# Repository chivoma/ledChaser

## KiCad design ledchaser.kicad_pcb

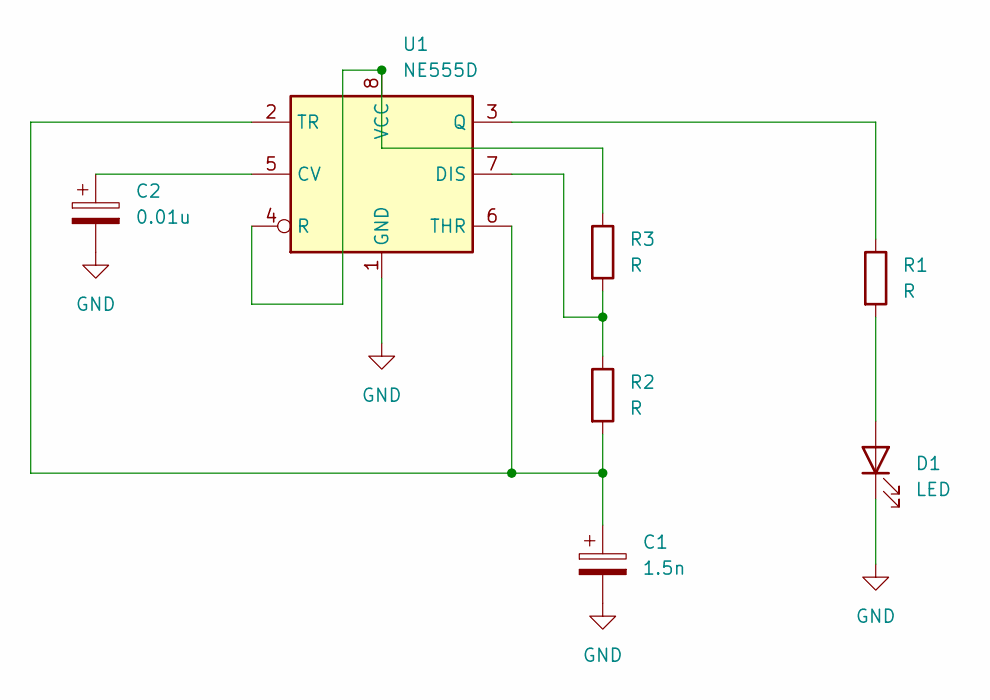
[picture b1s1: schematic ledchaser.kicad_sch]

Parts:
C1: 1.5n; CP_Elec_3x5.3
C2: 0.01u; CP_Elec_3x5.3
D1: LED; LED_D3.0mm
R1, R2, R3: R; R_0402_1005Metric
U1: NE555D; SOIC-8_3.9x4.9mm_P1.27mm

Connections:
GND: C1.2, C2.2, D1.1 (K), U1.1 (GND)
unnamed: D1.2 (A), R1.2
unnamed: C2.1, U1.5 (CV)
unnamed: R2.1, R3.2, U1.7 (DIS)
unnamed: R1.1, U1.3 (Q)
unnamed: R3.1, U1.4 (R), U1.8 (VCC)
unnamed: C1.1, R2.2, U1.2 (TR), U1.6 (THR)

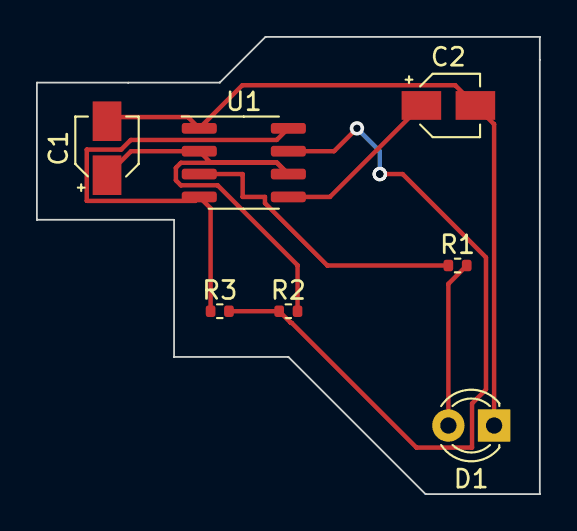
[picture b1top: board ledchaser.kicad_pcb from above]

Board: 2 copper layers, 27.9 x 25.4 mm, 7 parts (0 on the bottom side), 7 nets.
